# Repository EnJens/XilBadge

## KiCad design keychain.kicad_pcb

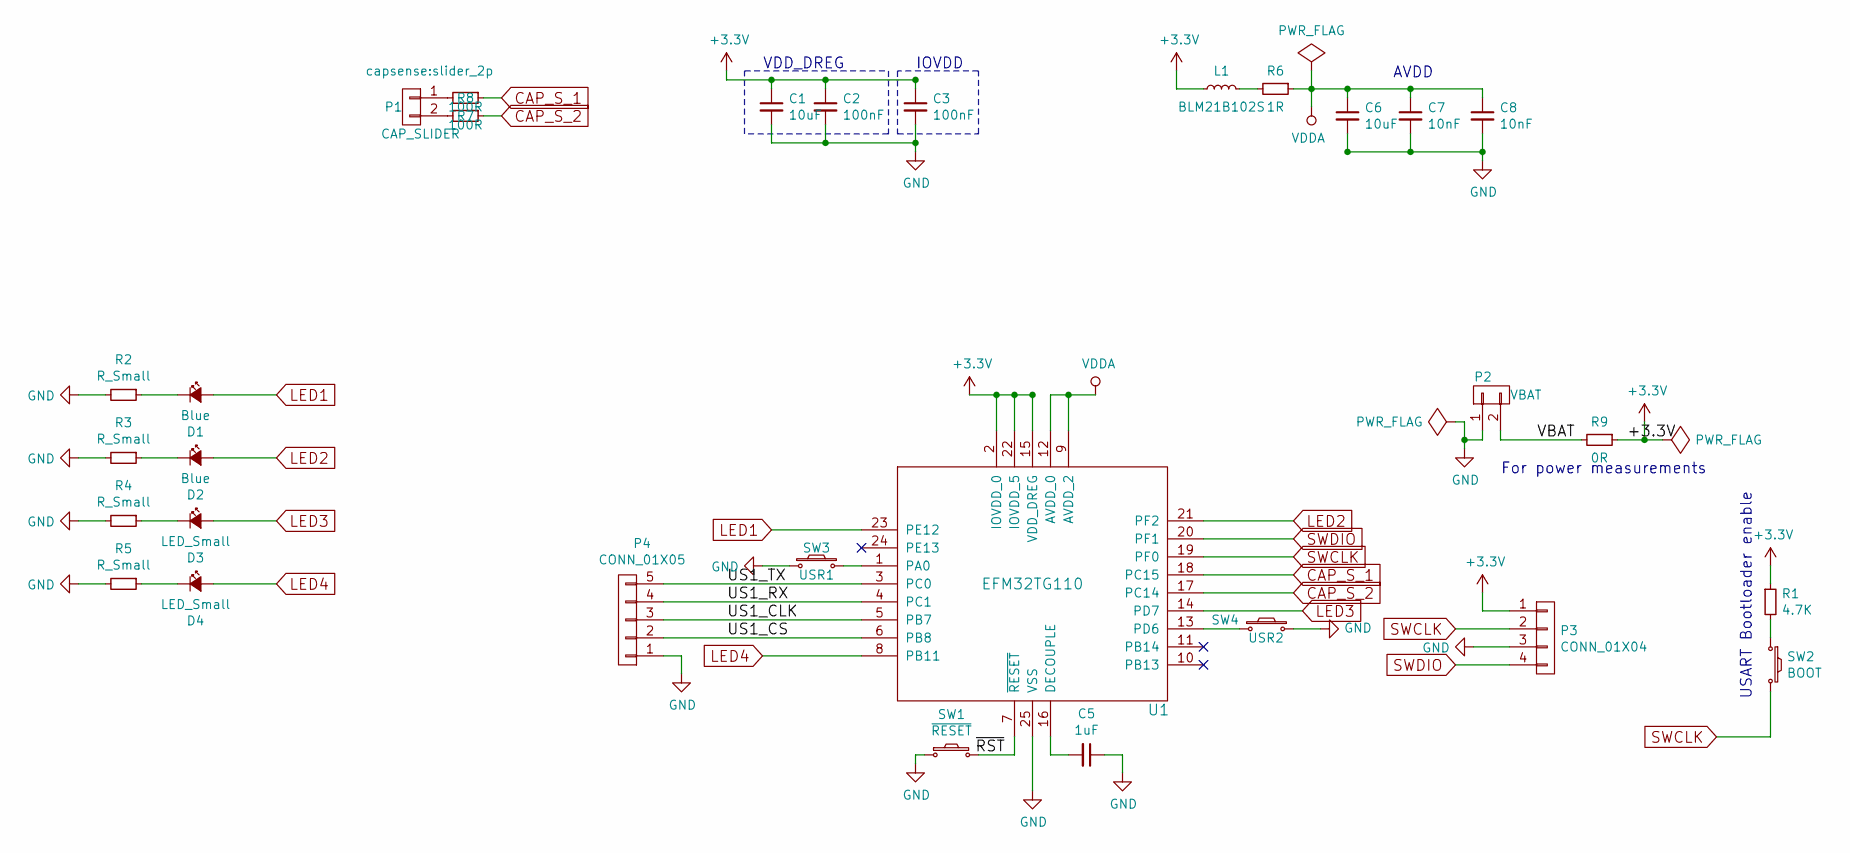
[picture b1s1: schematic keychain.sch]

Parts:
C1, C6: 10uF; C_0603
C2, C3: 100nF; C_0603
C5: 1uF; C_0603
C7, C8: 10nF; C_0603
D1, D2: Blue; LED_0603
D3, D4: LED_Small; LED_0603
L1: BLM21B102S; C_0805
P1: CAP_SLIDER; slider_2p
P2: VBAT; CR2032_SMD
P3: CONN_01X04; CONN_01X04_1.27mm
P4: CONN_01X05; CONN_01X05_SMDISH
R1: 4.7K; R_0603
R2, R3, R4, R5: R_Small; R_0603
R6: 1R; R_0603
R7, R8: 100R; R_0603
R9: 0R; R_0603
SW1: ~RESET~; Tactile_Push_Button_SMD_3x3x1.5mm.kicad_mod
SW2: BOOT; Tactile_Push_Button_SMD_3x3x1.5mm.kicad_mod
SW3: USR1; SmallButton
SW4: USR2; SmallButton
U1: EFM32TG110; QFN-24-1EP_5x5mm_Pitch0.65mm

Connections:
+3V3: C1.1, C2.1, C3.1, L1.1, P3.1, R1.1, R9.1, U1.2 (IOVDD_0), U1.15 (VDD_DREG), U1.22 (IOVDD_5)
/US1_CLK: P4.3, U1.5 (PB7)
/US1_CS: P4.2, U1.6 (PB8)
/US1_RX: P4.4, U1.4 (PC1)
/US1_TX: P4.5, U1.3 (PC0)
/VBAT: P2.2, R9.2
/~RST~: SW1.2, U1.7 (~RESET~)
CAP_S_1: R8.1, U1.18 (PC15)
CAP_S_2: R7.1, U1.17 (PC14)
GND: C1.2, C2.2, C3.2, C5.1, C6.2, C7.2, C8.2, P2.1, P3.3, P4.1, R2.2, R3.2, R4.2, R5.2, SW1.1, SW3.1, SW4.2, U1.25 (VSS)
LED1: D1.2 (A), U1.23 (PE12)
LED2: D2.2 (A), U1.21 (PF2)
LED3: D3.2 (A), U1.14 (PD7)
LED4: D4.2 (A), U1.8 (PB11)
unnamed: C5.2, U1.16 (DECOUPLE)
unnamed: D1.1 (K), R2.1
unnamed: D2.1 (K), R3.1
unnamed: D3.1 (K), R4.1
unnamed: D4.1 (K), R5.1
unnamed: L1.2, R6.2
unnamed: P1.1, R8.2
unnamed: P1.2, R7.2
unnamed: R1.2, SW2.1
unnamed: SW3.2, U1.1 (PA0)
unnamed: SW4.1, U1.13 (PD6)
SWCLK: P3.2, SW2.2, U1.19 (PF0)
SWDIO: P3.4, U1.20 (PF1)
VDDA: C6.1, C7.1, C8.1, R6.1, U1.9 (AVDD_2), U1.12 (AVDD_0)

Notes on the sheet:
VDD_DREG
IOVDD
AVDD
USART Bootloader enable
For power measurements

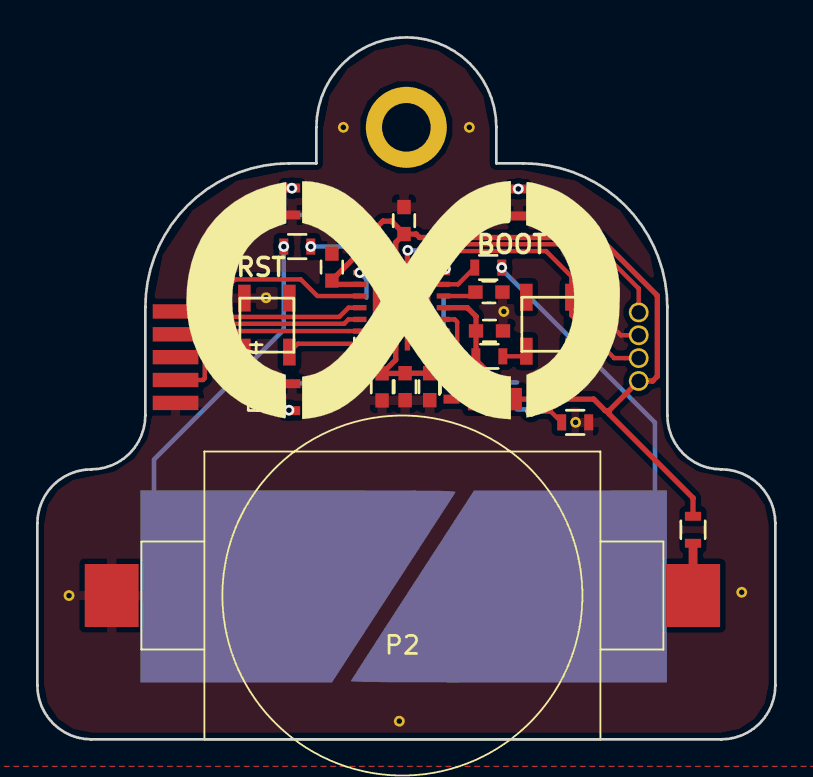
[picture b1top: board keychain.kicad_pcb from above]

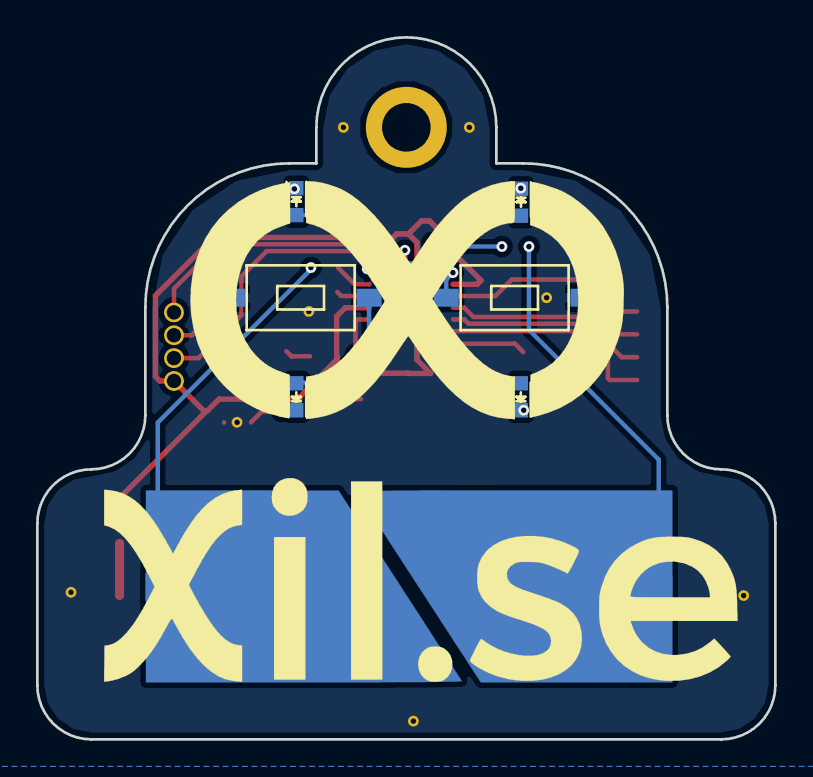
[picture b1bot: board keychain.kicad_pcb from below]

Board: 2 copper layers, 41.0 x 39.0 mm, 30 parts (7 on the bottom side), 28 nets.

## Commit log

2016-11-11 Switched to EFM32TG110, redid board layout
2016-11-12 More or less done.
2016-11-12 Moar changes
2016-11-12 Add 0R resistor for measuring current
2016-11-13 move capsense resistor to front side and reroute
2016-11-14 Rotate buttons to look nicer, fix missing reset connection
